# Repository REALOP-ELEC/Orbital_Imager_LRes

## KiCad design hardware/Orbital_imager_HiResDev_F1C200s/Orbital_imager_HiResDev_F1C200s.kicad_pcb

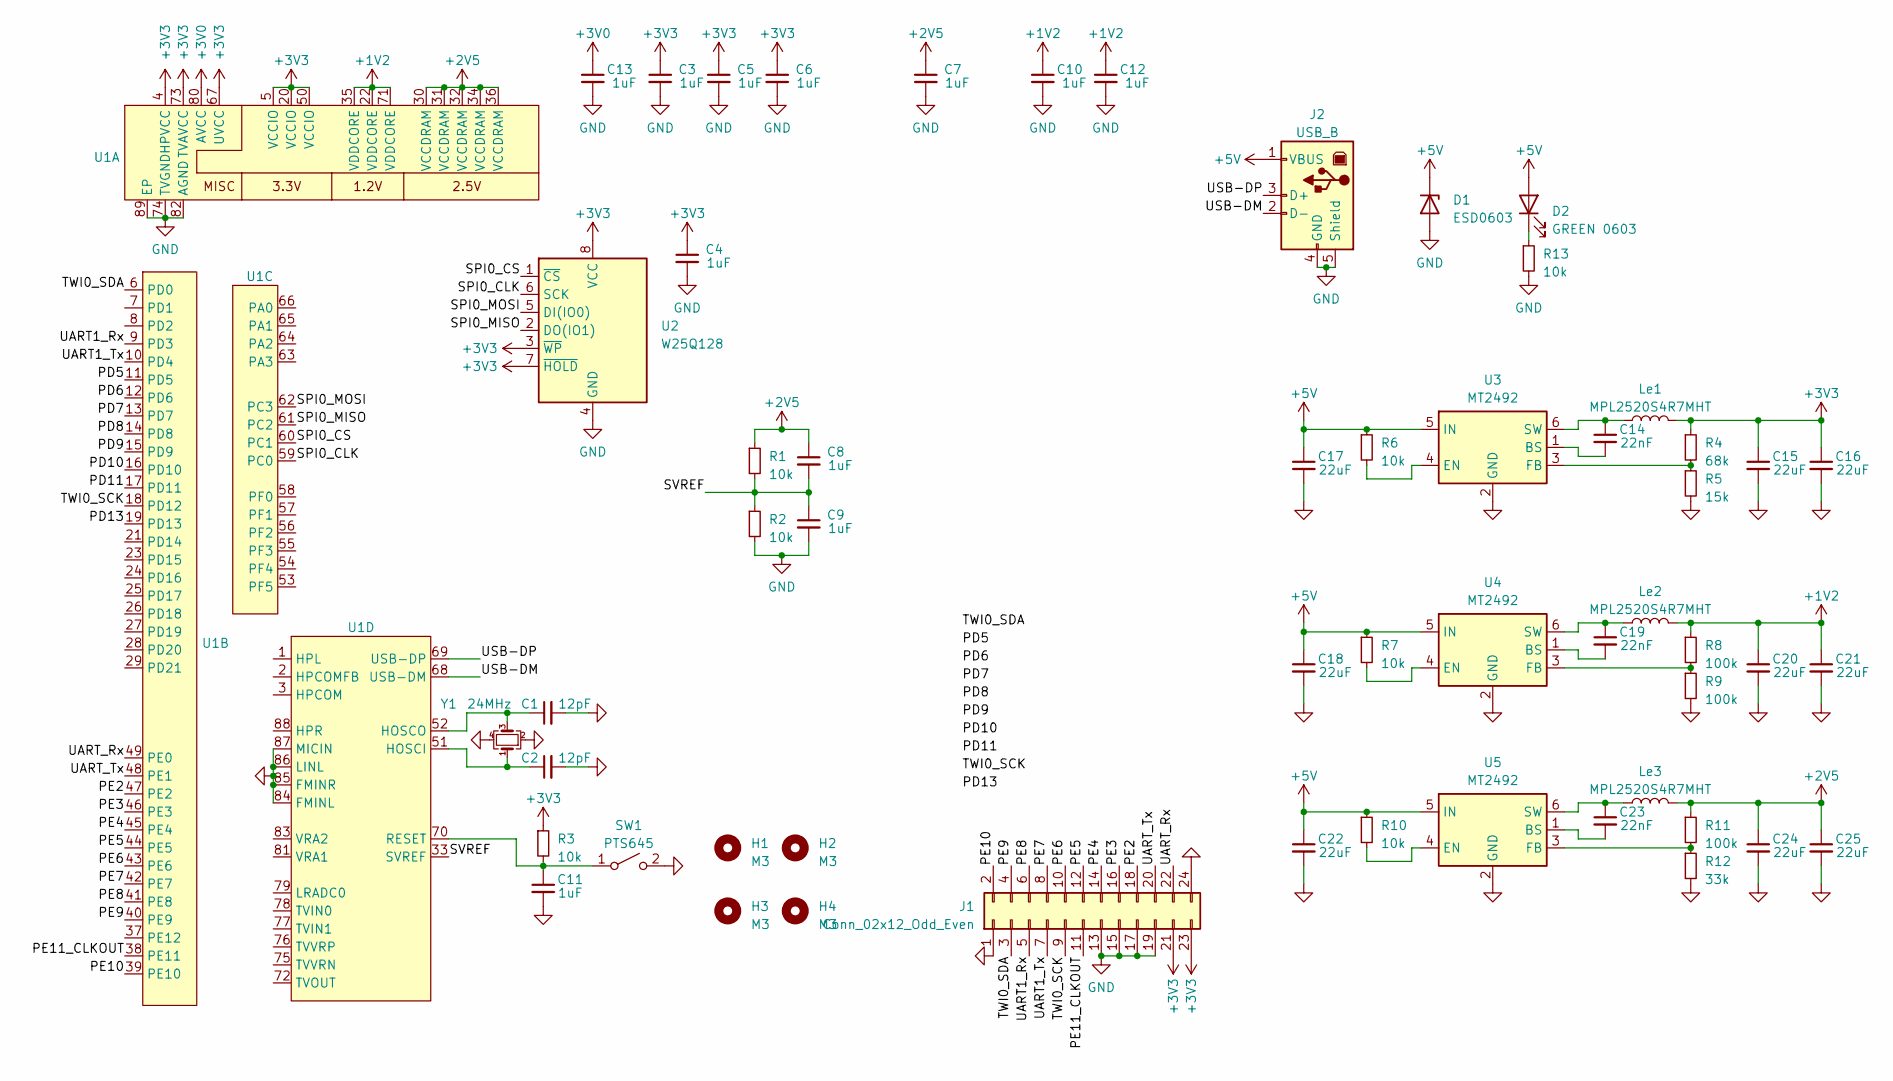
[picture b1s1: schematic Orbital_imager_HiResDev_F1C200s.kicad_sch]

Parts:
C1, C2: 12pF; C_0402_1005Metric
C3, C4, C5, C6, C7, C8, C9, C10, C11, C12, C13: 1uF; C_0402_1005Metric
C14, C19, C23: 22nF; C_0402_1005Metric
C15, C16, C17, C18, C20, C21, C22, C24, C25: 22uF; C_0805_2012Metric
D1: ESD0603; D_0603_1608Metric
D2: GREEN 0603; D_0603_1608Metric
H1, H2, H3, H4: M3; MountingHole_3.2mm_M3
J1: Conn_02x12_Odd_Even; PinSocket_2x12_P2.54mm_Vertical
J2: USB_B; USB_B_OST_USB-B1HSxx_Horizontal
Le1, Le2, Le3: MPL2520S4R7MHT; L_1008_2520Metric
R1, R2, R3, R6, R7, R10, R13: 10k; R_0402_1005Metric
R4: 68k; R_0402_1005Metric
R5: 15k; R_0402_1005Metric
R8, R9, R11: 100k; R_0402_1005Metric
R12: 33k; R_0402_1005Metric
SW1: PTS645; SW_SPST_PTS645
U1: QFN-88_EP_10x10_0.4mm_F1C200s
U2: W25Q128; SOIC-8_3.9x4.9mm_P1.27mm
U3, U4, U5: MT2492; SOT-23-6
Y1: 24MHz; Crystal_SMD_5032-4Pin_5.0x3.2mm

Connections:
+1V2: C10.1, C12.1, C20.1, C21.1, Le2.2, R8.1, U1.22 (VDDCORE), U1.35 (VDDCORE), U1.71 (VDDCORE)
+2V5: C7.1, C8.1, C24.1, C25.1, Le3.2, R1.1, R11.1, U1.30 (VCCDRAM), U1.31 (VCCDRAM), U1.32 (VCCDRAM), U1.34 (VCCDRAM), U1.36 (VCCDRAM)
+3V0: C13.1, U1.80 (AVCC)
+3V3: C3.1, C4.1, C5.1, C6.1, C15.1, C16.1, J1.21, J1.23, Le1.2, R3.1, R4.1, U1.4 (HPVCC), U1.5 (VCCIO), U1.20 (VCCIO), U1.50 (VCCIO), U1.67 (UVCC), U1.73 (TVAVCC), U2.3 (~WP), U2.7 (~HOLD), U2.8 (VCC)
+5V: C17.1, C18.1, C22.1, D1.1 (K), D2.2 (A), J2.1 (VBUS), R6.1, R7.1, R10.1, U3.5 (IN), U4.5 (IN), U5.5 (IN)
/PD5: U1.11 (PD5)
/PD6: U1.12 (PD6)
/PD7: U1.13 (PD7)
/PD8: U1.14 (PD8)
/PD9: U1.15 (PD9)
/PD10: U1.16 (PD10)
/PD11: U1.17 (PD11)
/PD13: U1.19 (PD13)
/PE2: J1.18, U1.47 (PE2)
/PE3: J1.16, U1.46 (PE3)
/PE4: J1.14, U1.45 (PE4)
/PE5: J1.12, U1.44 (PE5)
/PE6: J1.10, U1.43 (PE6)
/PE7: J1.8, U1.42 (PE7)
/PE8: J1.6, U1.41 (PE8)
/PE9: J1.4, U1.40 (PE9)
/PE10: J1.2, U1.39 (PE10)
/PE11_CLKOUT: J1.11, U1.38 (PE11)
/SPI0_CLK: U1.59 (PC0), U2.6 (SCK)
/SPI0_CS: U1.60 (PC1), U2.1 (~CS)
/SPI0_MISO: U1.61 (PC2), U2.2 (DO(IO1))
/SPI0_MOSI: U1.62 (PC3), U2.5 (DI(IO0))
/SVREF: C8.2, C9.1, R1.2, R2.1, U1.33 (SVREF)
/TWI0_SCK: J1.9, U1.18 (PD12)
/TWI0_SDA: J1.3, U1.6 (PD0)
/UART1_Rx: J1.5, U1.9 (PD3)
/UART1_Tx: J1.7, U1.10 (PD4)
/UART_Rx: J1.22, U1.49 (PE0)
/UART_Tx: J1.20, U1.48 (PE1)
/USB-DM: J2.2 (D-), U1.68 (USB-DM)
/USB-DP: J2.3 (D+), U1.69 (USB-DP)
GND: C1.2, C2.2, C3.2, C4.2, C5.2, C6.2, C7.2, C9.2, C10.2, C11.2, C12.2, C13.2, C15.2, C16.2, C17.2, C18.2, C20.2, C21.2, C22.2, C24.2, C25.2, D1.2 (A), J1.1, J1.13, J1.15, J1.17, J1.19, J1.24, J2.4 (GND), J2.5 (Shield), R2.2, R5.2, R9.2, R12.2, R13.2, SW1.2 (B), U1.74 (TVGND), U1.82 (AGND), U1.84 (FMINL), U1.85 (FMINR), U1.86 (LINL), U1.87 (MICIN), U1.89 (EP), U2.4 (GND), U3.2 (GND), U4.2 (GND), U5.2 (GND), Y1.2, Y1.4
unnamed: D2.1 (K), R13.1
unnamed: C11.1, R3.2, SW1.1 (A), U1.70 (RESET)
unnamed: C2.1, U1.51 (HOSCI), Y1.1
unnamed: C1.1, U1.52 (HOSCO), Y1.3
unnamed: C14.2, U3.1 (BS)
unnamed: R6.2, U3.4 (EN)
unnamed: R4.2, R5.1, U3.3 (FB)
unnamed: C14.1, Le1.1, U3.6 (SW)
unnamed: C19.2, U4.1 (BS)
unnamed: R7.2, U4.4 (EN)
unnamed: R8.2, R9.1, U4.3 (FB)
unnamed: C19.1, Le2.1, U4.6 (SW)
unnamed: C23.2, U5.1 (BS)
unnamed: R10.2, U5.4 (EN)
unnamed: R11.2, R12.1, U5.3 (FB)
unnamed: C23.1, Le3.1, U5.6 (SW)

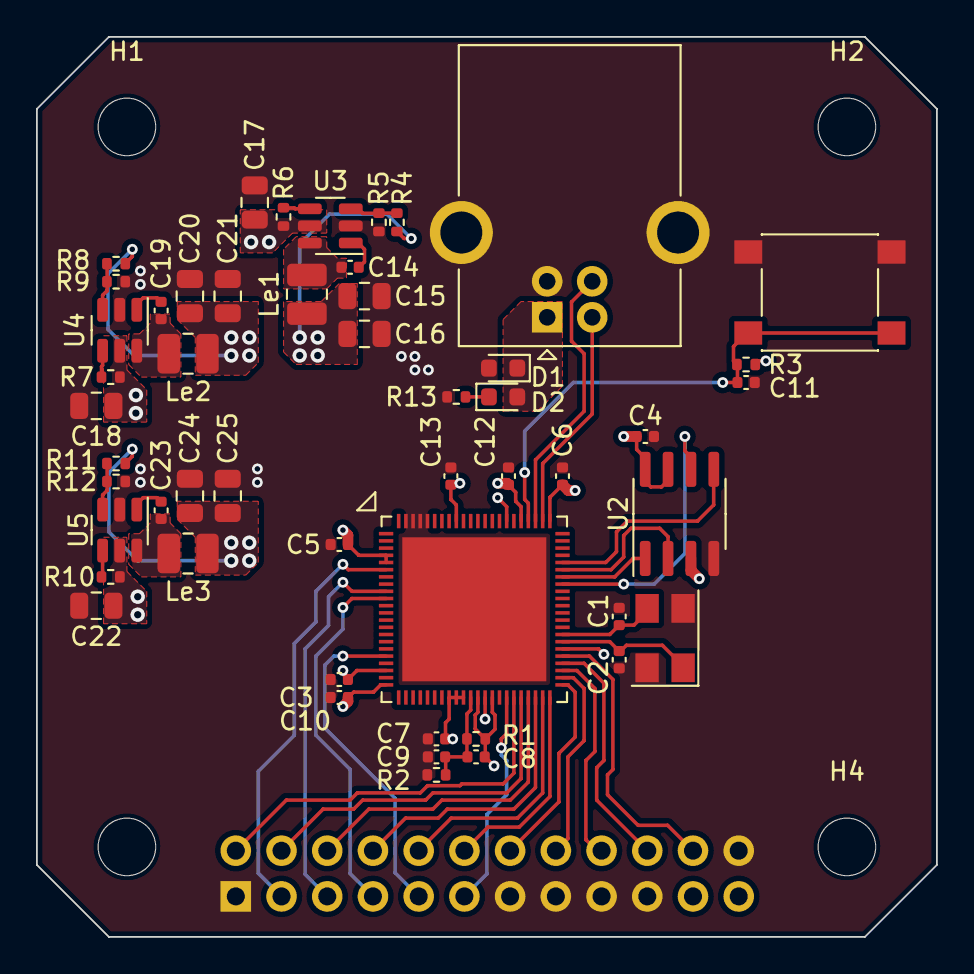
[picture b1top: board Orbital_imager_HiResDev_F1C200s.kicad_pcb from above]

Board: 4 copper layers, 50.0 x 50.0 mm, 56 parts (1 on the bottom side), 45 nets.

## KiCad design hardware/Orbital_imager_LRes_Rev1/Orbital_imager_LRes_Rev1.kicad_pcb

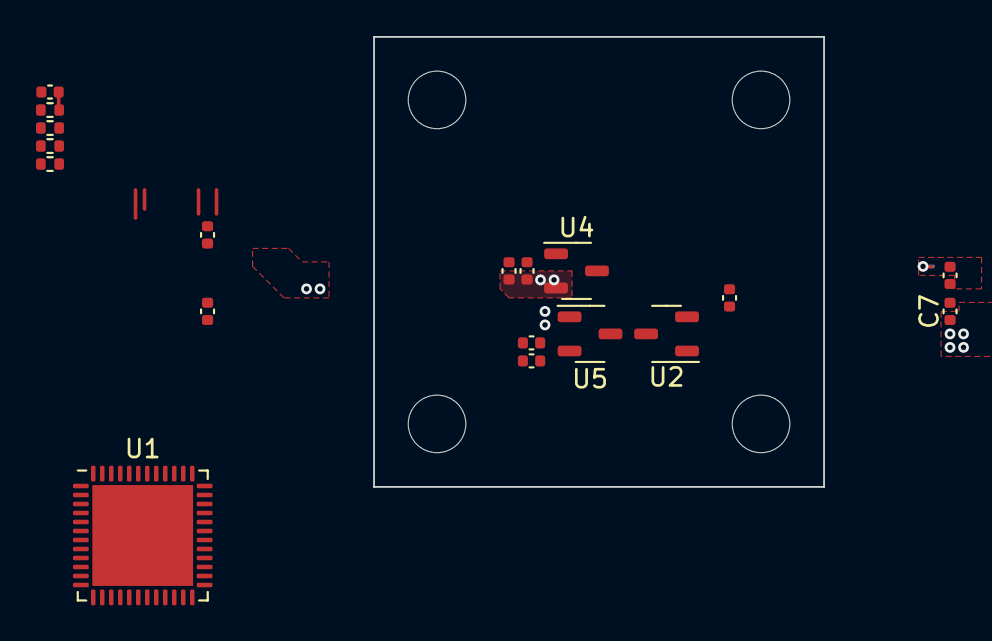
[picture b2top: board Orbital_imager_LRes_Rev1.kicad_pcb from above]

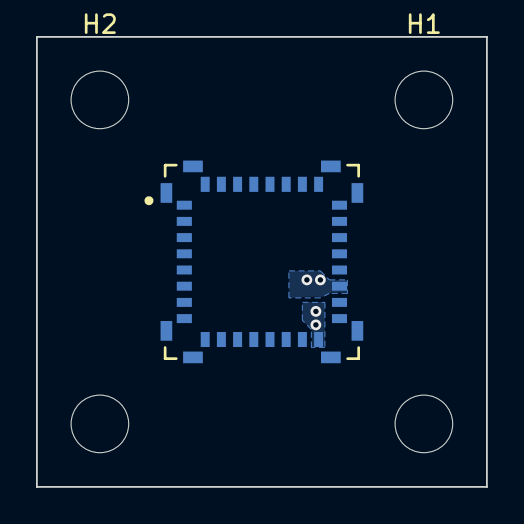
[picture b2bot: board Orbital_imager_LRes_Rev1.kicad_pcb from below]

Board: 4 copper layers, 25.0 x 25.0 mm, 23 parts (5 on the bottom side), 13 nets.

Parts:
C1, C2, C3, C4, C6, C7, C8, C9, C10, C11: 1uF; C_0402_1005Metric
H1, H2, H3, H4: M3; MountingHole_3.2mm_M3
R1: 100k; R_0402_1005Metric
R2, R3, R4: 10k; R_0402_1005Metric
U1: STM32G431CBUx; QFN-48-1EP_7x7mm_P0.5mm_EP5.6x5.6mm
U2, U4, U5: XC6206PxxxMR; SOT-23-3
U3: Flir_LEPTON; Molex-1050281001-MFG

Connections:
+1V2: C3.1, C6.1, U2.2 (VO), U3.7 (VDDC)
+2V8: C1.1, C9.1, U3.19 (VDD), U4.2 (VO)
+3V0: C2.1, C11.1, R1.1, R2.1, R3.2, R4.2, U1.1 (VBAT), U1.21 (VDDA), U1.23 (VDD), U1.35 (VDD), U1.48 (VDD), U3.16 (VDDIO), U5.2 (VO)
/SCL: R3.1, U1.38 (PA15), U3.21 (SCL)
/SDA: R4.1, U1.45 (PB7), U3.22 (SDA)
/SPI_CLK: U1.13 (PA5), U3.13 (SPI_CLK)
/SPI_CS: U1.12 (PA4), U3.14 (SPI_CS_L)
/SPI_MISO: U1.14 (PA6), U3.12 (SPI_MISO)
/SPI_MOSI: U1.15 (PA7), U3.11 (SPI_MOSI)
GND: C1.2, C2.2, C3.2, C4.2, C6.2, C7.2, C8.2, C9.2, C10.2, C11.2, U1.49 (VSS), U2.1 (GND), U3.1 (GND), U3.6 (GND), U3.8 (GND), U3.9 (GND), U3.10 (GND), U3.15 (GND), U3.18 (GND), U3.20 (GND), U3.25 (GND), U3.27 (GND), U3.30 (GND), U4.1 (GND), U5.1 (GND)
unnamed: R1.2, U3.23 (PWR_DWN_L)
unnamed: C4.1, R2.2, U3.24 (RESET_L)
VCC: C7.1, C8.1, C10.1, U2.3 (VI), U4.3 (VI), U5.3 (VI)

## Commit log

2023-05-10 added a lot of comments
2023-05-11 added hardware + config firmware
2023-05-13 ported to C
